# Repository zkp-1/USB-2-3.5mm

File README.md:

# USB-2-3.5mm
Personal Project to drive analog speakers from USB Type C.
##
I utilized a Cmedia CM108B audio IC and a MAX97720A Amplifier IC. The USB Type C connector is wired with resistors on CC1 and CC2 to allow power draw from the Host. The Cmedia IC then sends an identifier notifying the Host that the device is an audio device, making it load drivers and prepare for audio playthrough. A 90Ω impedance was aimed for in the design, to allow optimal operation on the differential USB data rails. At last, the IC sends the Audio data through its own DACs and internal amplifiers, converting it to analog and being able to be used at the intended 3.5mm output. 

The MAX97220A is set with a gain of 3.52dB and an input impedance of 10k. The output of the MAX IC is wired directly onto the 3.5mm and has an integrated anti-crackle and pop solution inside the IC, which was my main drive to using this IC for amplification.
# PCB 3D KiCAD Renders
1. 

2.

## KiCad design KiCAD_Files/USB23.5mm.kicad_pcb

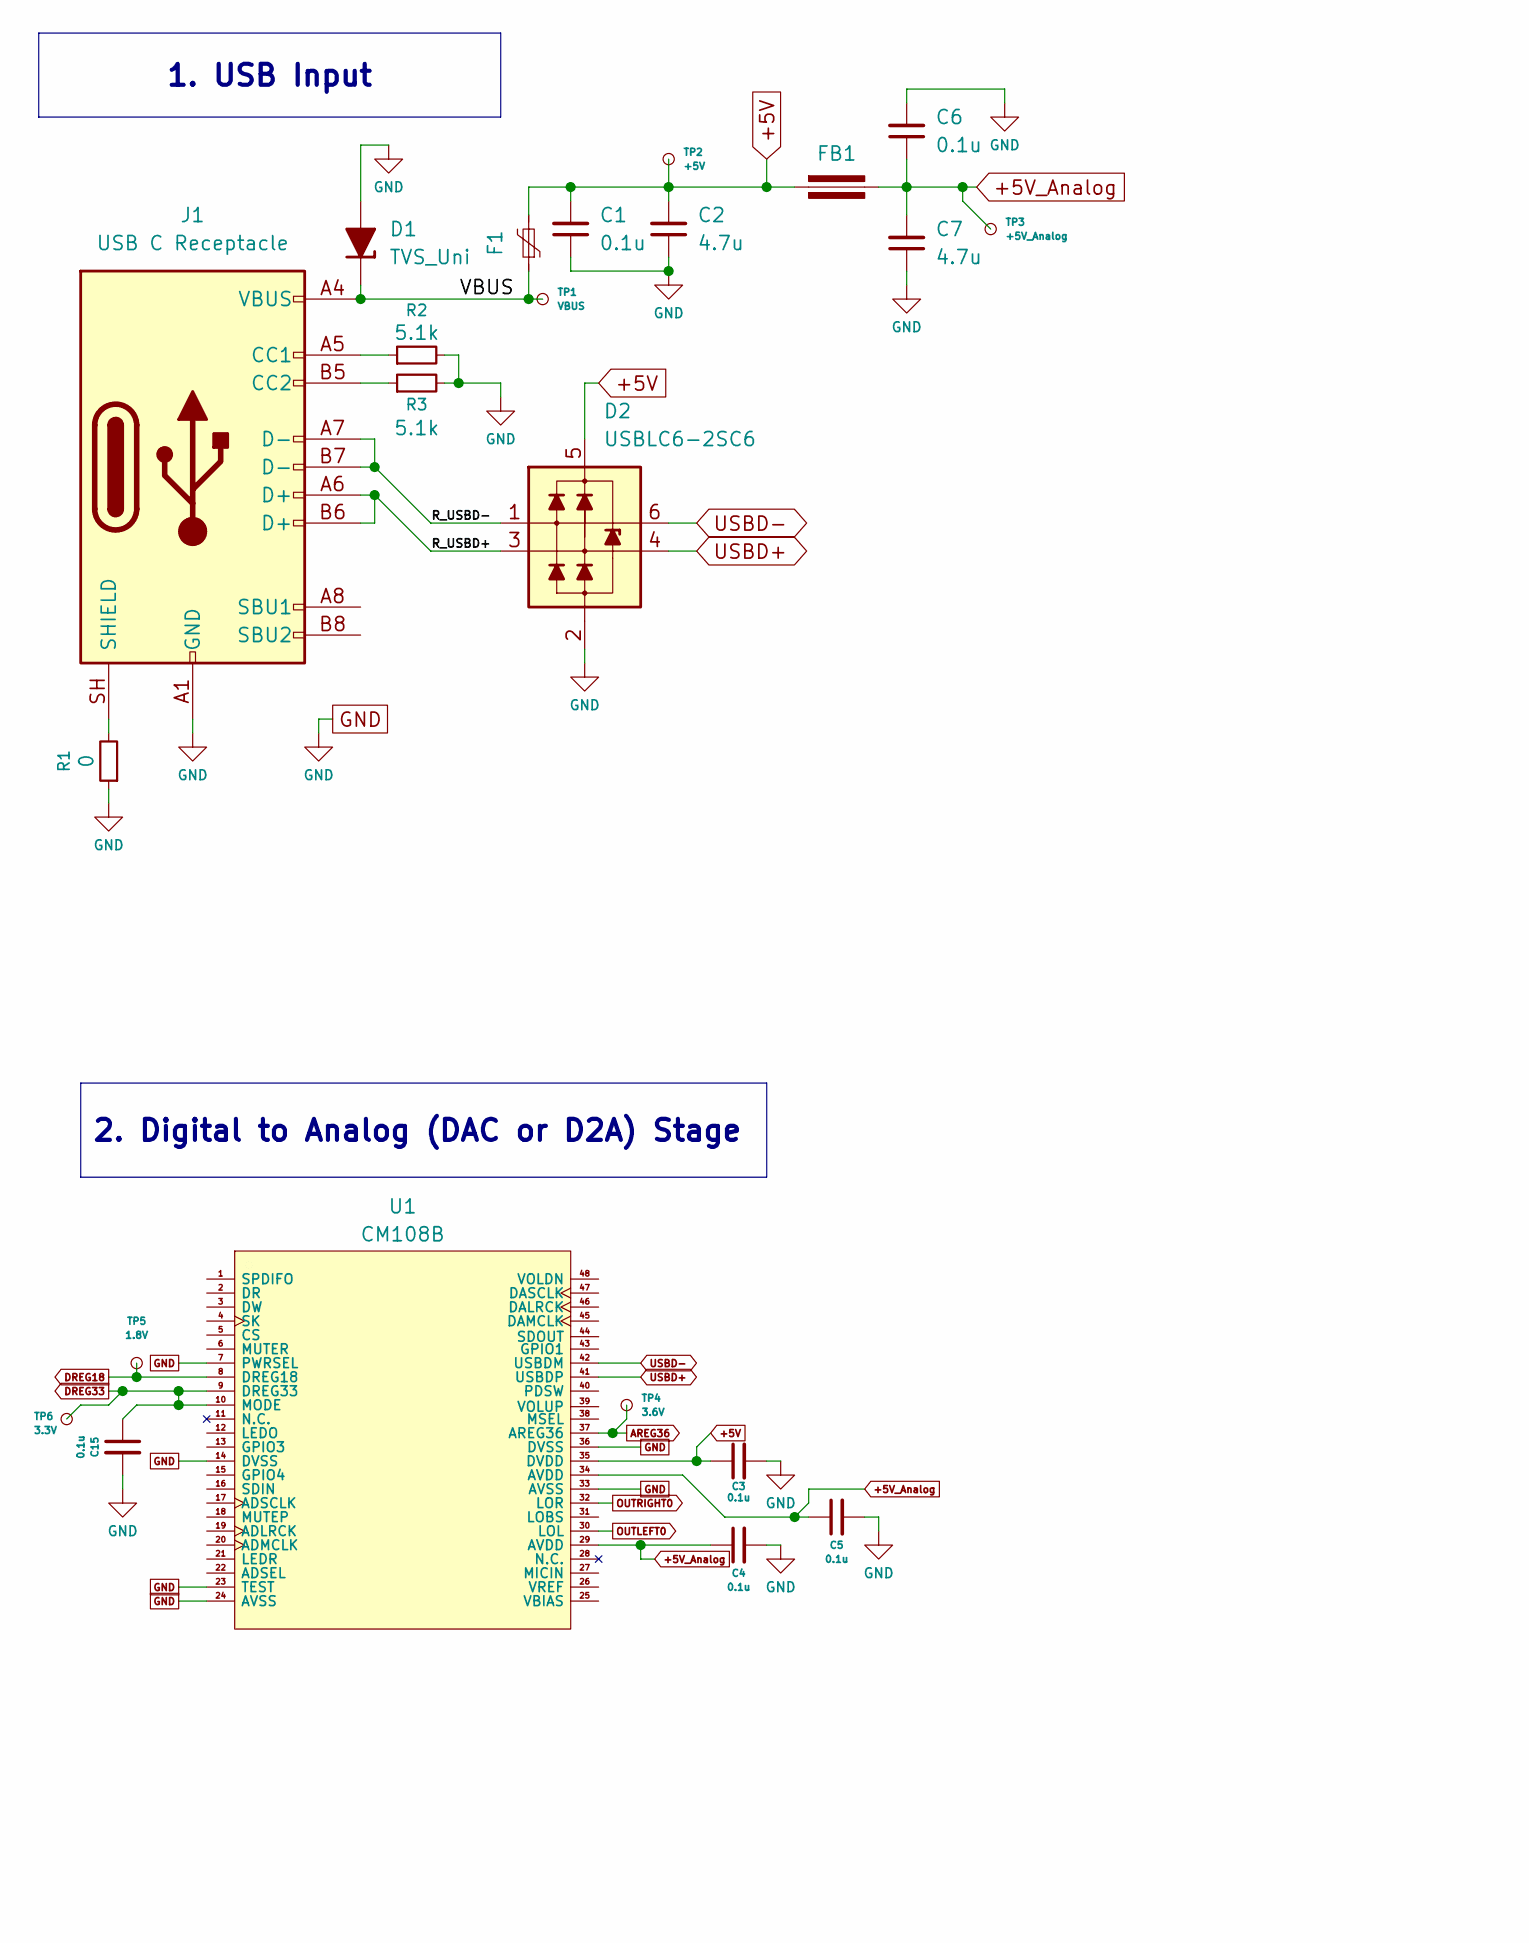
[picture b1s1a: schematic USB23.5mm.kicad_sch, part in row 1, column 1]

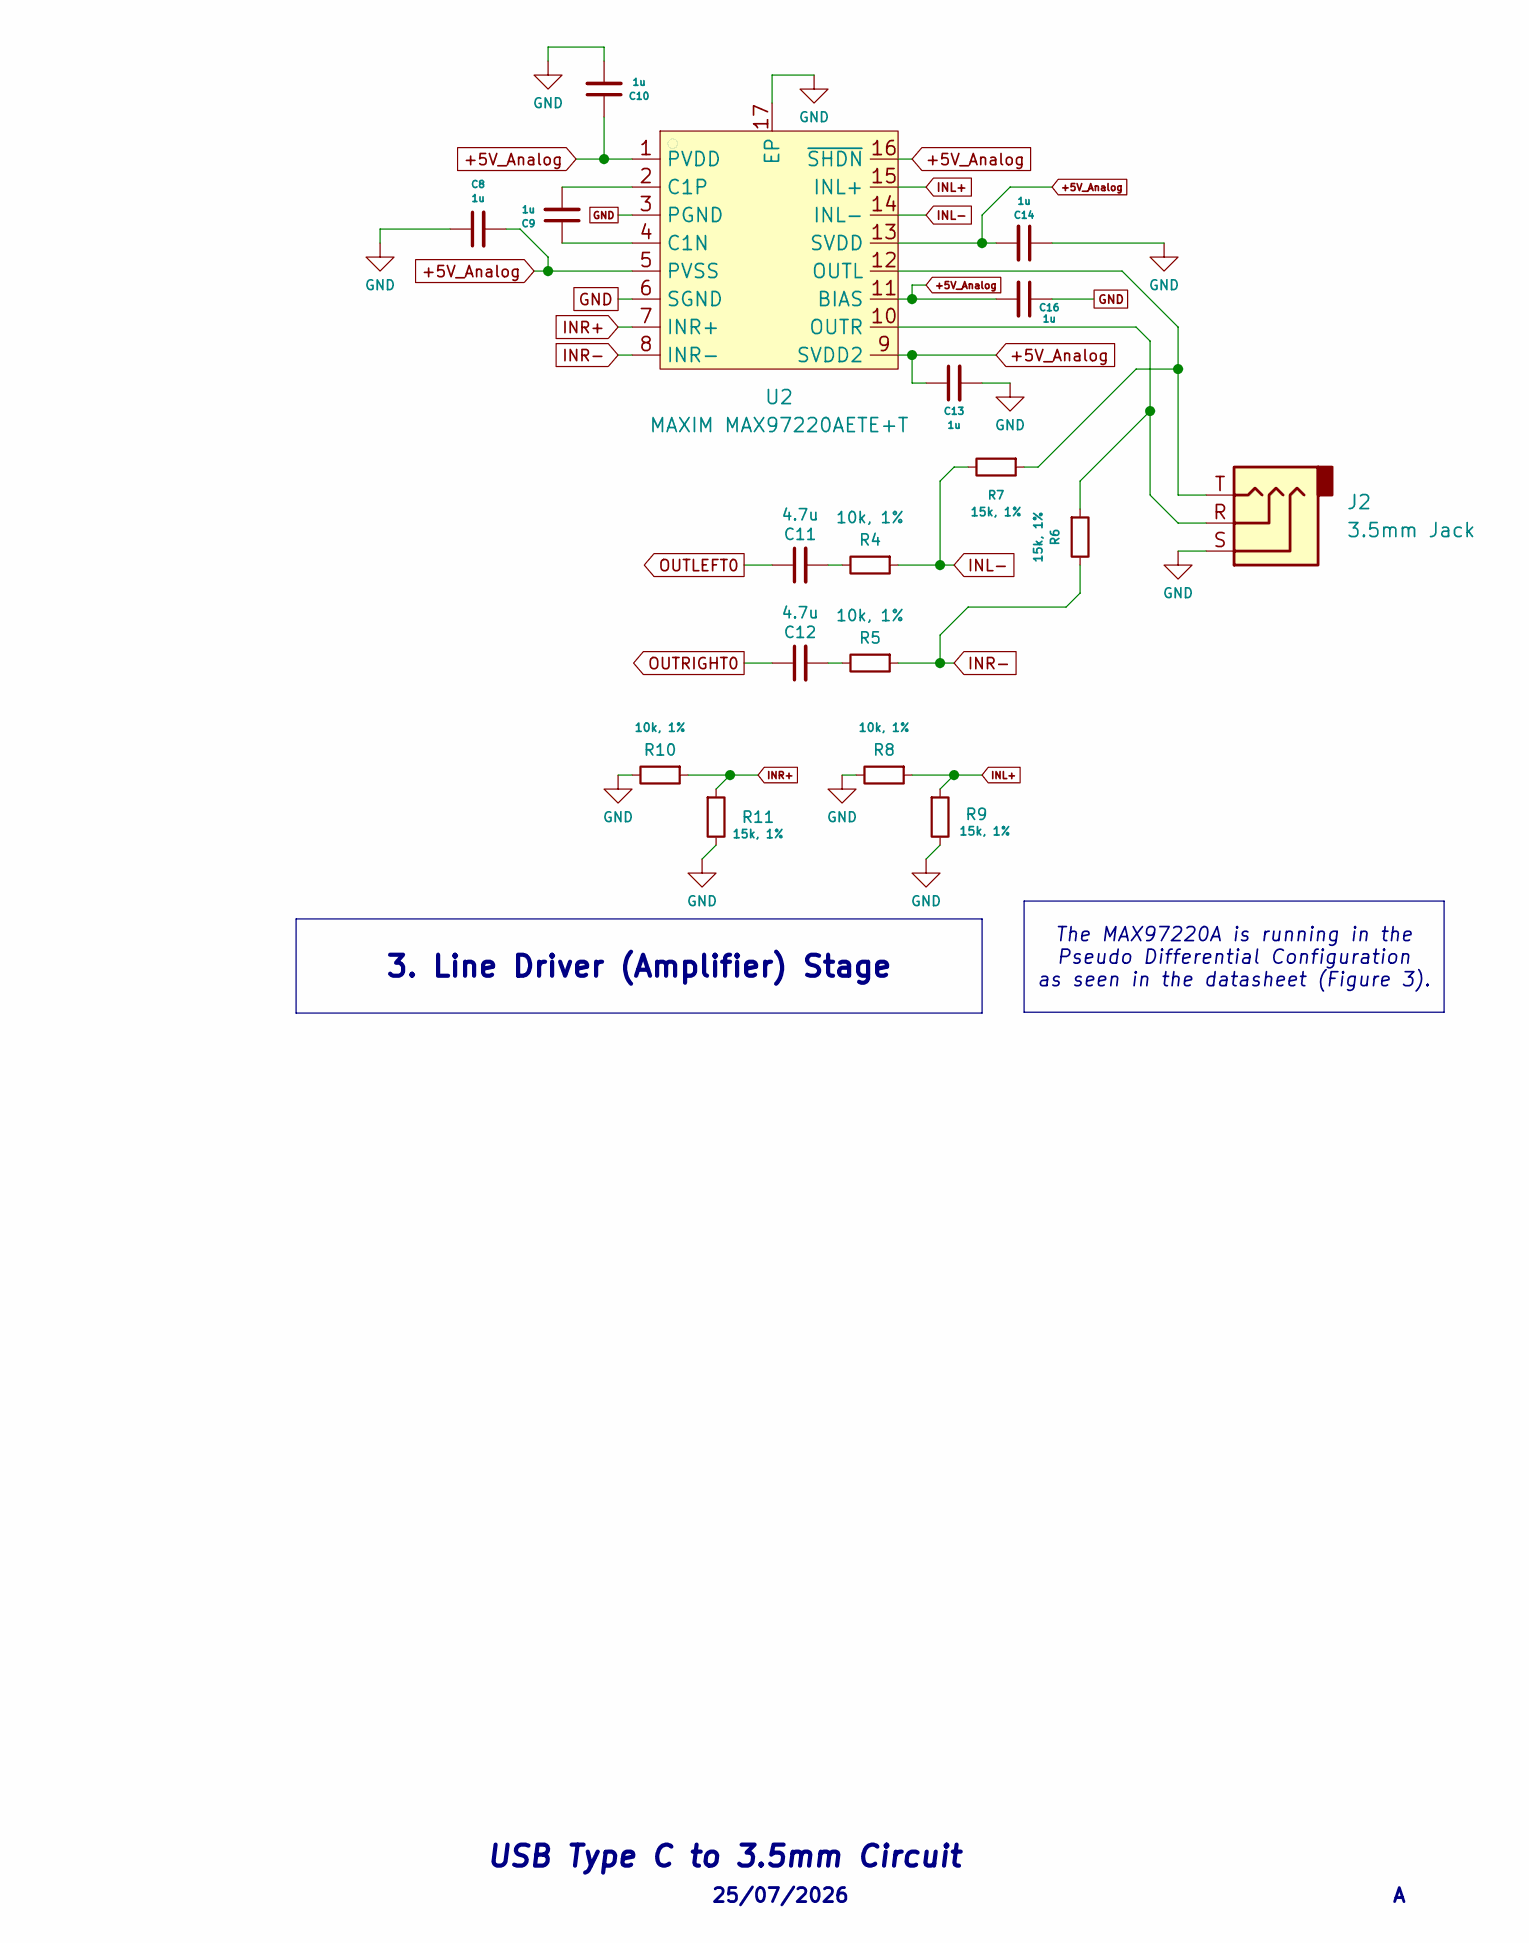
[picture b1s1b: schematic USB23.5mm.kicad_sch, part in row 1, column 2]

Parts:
C1, C3, C4, C5, C6, C15: 0.1u; C_0805_2012Metric_Pad1.18x1.45mm_HandSolder
C2, C7, C11, C12: 4.7u; C_0805_2012Metric_Pad1.18x1.45mm_HandSolder
C8, C9, C10, C13, C14, C16: 1u; C_0805_2012Metric_Pad1.18x1.45mm_HandSolder
D1: TVS_Uni; D_SOD-123F
D2: USBLC6-2SC6; SOT-23-6
F1: Polyfuse_S; Fuse_2920_7451Metric_Pad2.10x5.45mm_HandSolder
FB1: Ferrite_Bead; Ferrite_0805_2012Metric
J1: USB C Receptacle; USB_C_Receptacle_XKB_U262-16XN-4BVC11
J2: 3.5mm Jack; Jack_3.5mm_CUI_SJ-3523-SMT_Horizontal
R1: 0; R_0805_2012Metric
R2, R3: 5.1k; R_0805_2012Metric
R4, R5, R8, R10: 10k, 1%; R_0805_2012Metric
R6, R7, R9, R11: 15k, 1%; R_0805_2012Metric
TP1: VBUS; TestPoint_Pad_D1.5mm
TP2: +5V; TestPoint_Pad_D1.5mm
TP3: +5V_Analog; TestPoint_Pad_D1.5mm
TP4: 3.6V; TestPoint_Pad_D1.5mm
TP5: 1.8V; TestPoint_Pad_D1.5mm
TP6: 3.3V; TestPoint_Pad_D1.5mm
U1: CM108B; LQFP-48_7x7mm_P0.5mm
U2: MAXIM MAX97220AETE+T; QFN-16-1EP_3x3mm_P0.5mm_EP1.45x1.45mm

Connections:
+5V: C1.2, C2.2, C3.1, D2.5 (VP), F1.2, FB1.1, TP2.1 (1_1), U1.35 (DVDD)
+5V_Analog: C4.1, C5.1, C6.1, C7.2, C8.2, C10.1, C13.1, C14.2, C16.2, FB1.2, TP3.1 (1_1), U1.29 (AVDD), U1.34 (AVDD), U2.1 (PVDD), U2.5 (PVSS), U2.9 (SVDD2), U2.11 (BIAS), U2.13 (SVDD), U2.16 (~SHDN)
/R_USBD+: D2.3 (L2), J1.A6 (D+), J1.B6 (D+)
/R_USBD-: D2.1 (L1), J1.A7 (D-), J1.B7 (D-)
/VBUS: D1.1 (K), F1.1, J1.A4 (VBUS), J1.A9 (VBUS), J1.B4 (VBUS), J1.B9 (VBUS), TP1.1 (1_1)
AREG36: TP4.1 (1_1), U1.37 (AREG36)
DREG18: TP5.1 (1_1), U1.8 (DREG18)
DREG33: C15.1, TP6.1 (1_1), U1.9 (DREG33), U1.10 (MODE)
GND: C1.1, C2.1, C3.2, C4.2, C5.2, C6.2, C7.1, C8.1, C10.2, C13.2, C14.1, C15.2, C16.1, D1.2 (A), D2.2 (VN), J1.A1 (GND), J1.A12 (GND), J1.B1 (GND), J1.B12 (GND), J2.S, R1.1, R2.2, R3.2, R8.2, R9.2, R10.2, R11.2, U1.7 (PWRSEL), U1.14 (DVSS), U1.23 (TEST), U1.24 (AVSS), U1.33 (AVSS), U1.36 (DVSS), U2.3 (PGND), U2.6 (SGND), U2.17 (EP)
INL+: R8.1, R9.1, U2.15 (INL+)
INL-: R4.1, R7.2, U2.14 (INL-)
INR+: R10.1, R11.1, U2.7 (INR+)
INR-: R5.1, R6.2, U2.8 (INR-)
unnamed: C11.2, R4.2
unnamed: C12.2, R5.2
unnamed: J1.A5 (CC1), R2.1
unnamed: J1.B5 (CC2), R3.1
unnamed: J1.SH (SHIELD), R1.2
unnamed: C9.1, U2.4 (C1N)
unnamed: C9.2, U2.2 (C1P)
unnamed: J2.T, R7.1, U2.12 (OUTL)
unnamed: J2.R, R6.1, U2.10 (OUTR)
OUTLEFT0: C11.1, U1.30 (LOL)
OUTRIGHT0: C12.1, U1.32 (LOR)
USBD+: D2.4 (L2), U1.41 (USBDP)
USBD-: D2.6 (L1), U1.42 (USBDM)

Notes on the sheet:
25/07/2026
USB Type C to 3.5mm Circuit
1. USB Input
2. Digital to Analog (DAC or D2A) Stage
The MAX97220A is running in the Pseudo Differential Configuration as seen in the datasheet (Figure 3).
3. Line Driver (Amplifier) Stage

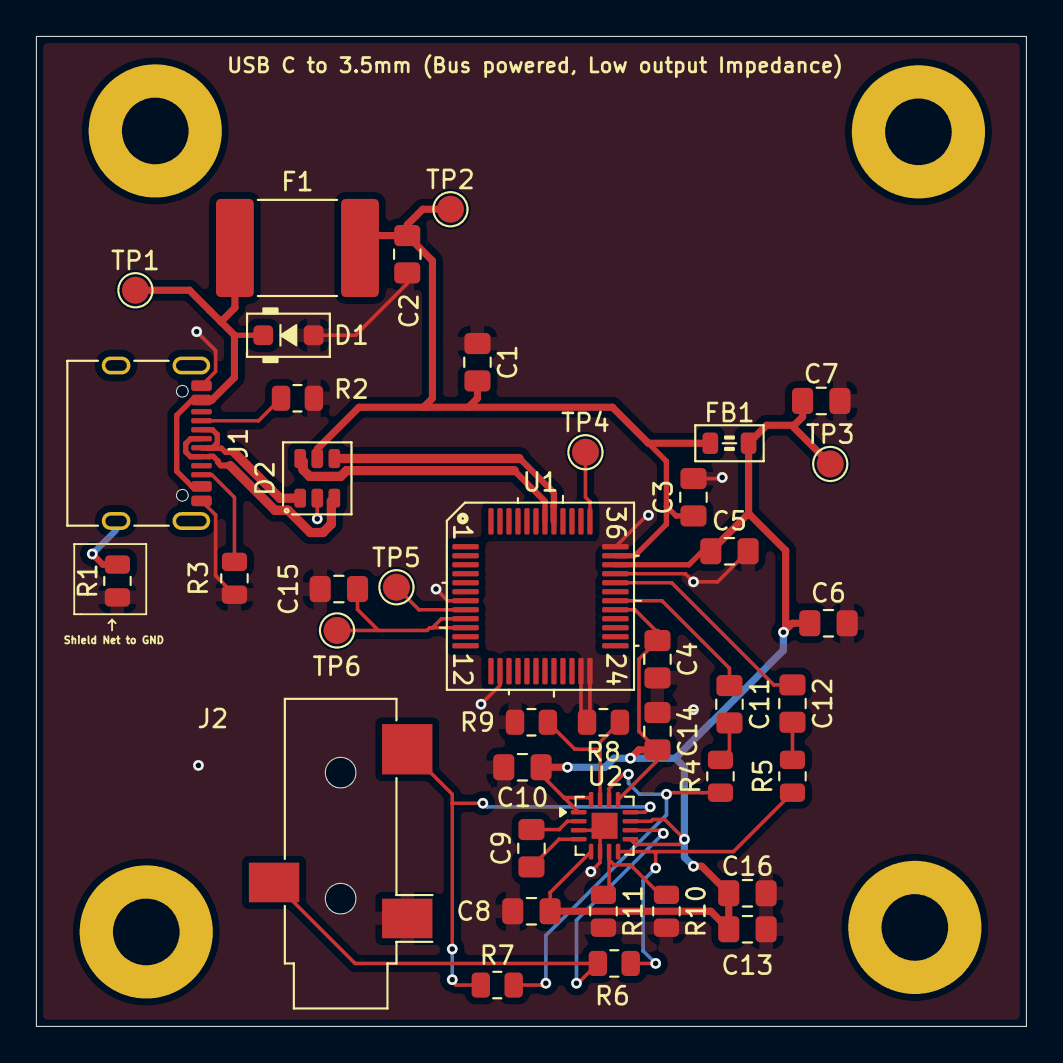
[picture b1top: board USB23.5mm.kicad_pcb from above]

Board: 2 copper layers, 55.0 x 55.0 mm, 41 parts (0 on the bottom side), 26 nets.

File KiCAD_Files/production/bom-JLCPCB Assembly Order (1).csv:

JLCPCB BOM Tool - BOM Matching,,,,,,,,,,,,,,,,,
BOM name：bom-JLCPCB Assembly Order.xlsx,,,Download Time：2026-07-26 06:23:22,,,,"* Our matching results are updated in real-time, but stock and prices may change. 
If it's been over 24 hours, please re-match before placing your order.",,,,,,,,,,
PCB Assembled Qty：5,,,Est. Total Price：30.8657,,,,,,,,,,,,,,
Your BOM,,,,,Matched Parts,,,,,,,Order Information,,,,,
Top Designator,Bottom Designator,Comment,Footprint,JLCPCB Part #,Matches,Part # ,Manufacturer,Footprint,Description,Category,Warning,JLCPCB Part #,Product link,Lib Type,Qty,Source,Total Price ($)
"C1,C15,C3,C4,C5,C6",,0.1u,0805,,Select by Customer,TCC0805X7R104K500DT,CCTC,0805,100nF 50V X7R ±10% 0805 Multilayer Ceramic Capacitors MLCC - SMD/SMT ROHS,Multilayer Ceramic Capacitors MLCC - SMD/SMT,1.The comment (TCC0805X7R104K500DT) of this part does not match the one (0.1u) provided in your BOM. Please confirm;,C282732,https://jlcpcb.com/partdetail/CCTC-TCC0805X7R104K500DT/C282732,Extended,40,40 JLCPCB,0.496
"C10,C13,C14,C16,C8,C9",,1u,0805,,Select by Customer,CGA0805X7R105K500KT,HRE,0805,1uF 50V X7R ±10% 0805 Multilayer Ceramic Capacitors MLCC - SMD/SMT ROHS,Multilayer Ceramic Capacitors MLCC - SMD/SMT,1.The comment (CGA0805X7R105K500KT) of this part does not match the one (1u) provided in your BOM. Please confirm;,C49056147,https://jlcpcb.com/partdetail/HRE-CGA0805X7R105K500KT/C49056147,Extended,36,36 JLCPCB,0.4284
"C11,C12,C2,C7",,4.7u,0805,,Select by Customer,TCC0805X7R475M500FT,CCTC,0805,4.7uF 50V X7R ±20% 0805 Multilayer Ceramic Capacitors MLCC - SMD/SMT ROHS,Multilayer Ceramic Capacitors MLCC - SMD/SMT,1.The comment (TCC0805X7R475M500FT) of this part does not match the one (4.7u) provided in your BOM. Please confirm;,C20416437,https://jlcpcb.com/partdetail/CCTC-TCC0805X7R475M500FT/C20416437,Extended,26,26 JLCPCB,3.484
D1,,TVS_Uni,D_SOD-123F,,Select by Customer,M4SMF15CA,Slkor(SLKORMICRO Elec.),SOD-123FL,15V 18.5V 180A@8/20us 1uA 26V 500pF Bidirectional TVS SOD-123FL ESD and Surge Protection (TVS/ESD) ROHS,,,C46061815,https://jlcpcb.com/partdetail/Slkor_SLKORMICRO_Elec-M4SMF15C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,Extended,15,15 JLCPCB,0.624
D2,,USBLC6-2SC6,SOT-23-6,,Select by System,USBLC6-2SC6,TECH PUBLIC,SOT-23-6,-55℃~+125℃ 0.35pF 12V 150W 2 5V 6A 6V 80nA ESD IEC 61000-4-2、IEC 61000-4-5、IEC 61000-4-4 Unidirectional SOT-23-6 ESD and Surge Protection (TVS/ESD) ROHS,ESD And Surge Protection (TVS/ESD),,C2827654,https://jlcpcb.com/partdetail/TECHPUBLIC-USBLC62SC6/C2827654,Extended,9,9 JLCPCB,0.3978
F1,,Polyfuse_S,2920,,Select by Customer,2920L500/6GR,LUTE,2920,-40℃~+85℃ 1.6mm 10A 2.5W 31mΩ 40A 5.44mm 5A 5mΩ 5s 6V 7.98mm 2920 Resettable Fuses ROHS,Resettable Fuses,,C19193059,https://jlcpcb.com/partdetail/LUTE-2920L5006GR/C19193059,Extended,5,5 JLCPCB,0.744
FB1,,Ferrite_Bead,Ferrite_0805_2012Metric,,Select by Customer,ZECB201209A121-4A000,ZE,0805,1 120Ω@100MHz 4A 50mΩ ±25% 0805 Ferrite Beads ROHS,Inductors (SMD),,C2943443,https://jlcpcb.com/partdetail/ZE-ZECB201209A1214A000/C2943443,Extended,20,20 JLCPCB,0.89
J1,,USBCReceptacle,USB_C_Receptacle_XKB_U262-16XN-4BVC11,,Select by Customer,HX TYPE-C 16PIN,hanxia,SMD,"-30℃~+80℃ 1 1.68mm 16P 20V 3A 5,000 times 7.35mm Black Female Surface Mount, Right Angle Type-C USB 3.1 SMD USB Connectors ROHS",USB Connectors,,C5178539,https://jlcpcb.com/partdetail/hanxia-HX_TYPE_C16PIN/C5178539,Extended,5,5 JLCPCB,0.375
J2,,3.5mmJack,Jack_3.5mm_CUI_SJ-3523-SMT_Horizontal,,Select by Customer,PJ-320B,SOFNG,SMD,-25℃~+75℃ 24V 25mA 3.5mm Headphone Jack Phosphor Bronze SMD Audio Connectors ROHS,Audio Connectors (Headphones),,C22355831,https://jlcpcb.com/partdetail/SOFNG-PJ320B/C22355831,Extended,5,5 JLCPCB,0.2455
R1,,0,0805,,Select by Customer,0805W8F0000T5E,UNI-ROYAL(Uniroyal Elec),0805,-55℃~+155℃ 0Ω 125mW 150V Thick Film Resistor ±1% ±800ppm/℃ 0805 Chip Resistor - Surface Mount ROHS,Chip Resistor - Surface Mount,1.The comment (0805W8F0000T5E) of this part does not match the one (0) provided in your BOM. Please confirm;,C17477,https://jlcpcb.com/partdetail/18165-0805W8F0000T5E/C17477,Basic,20,20 JLCPCB,0.2
"R2,R3",,5.1k,0805,,Select by Customer,GR0805F5K1T5G00,GiantOhm,0805,-55℃~+155℃ 125mW 150V 5.1kΩ Thick Film Resistor ±1% 0805 Chip Resistor - Surface Mount ROHS,,1.The comment (GR0805F5K1T5G00) of this part does not match the one (5.1k) provided in your BOM. Please confirm;,C49653299,https://jlcpcb.com/partdetail/GiantOhm-GR0805F5K1T5G00/C49653299,Extended,20,20 JLCPCB,0.034
"R10,R4,R5,R8",,"10k,1%",0805,,Select by Customer,HRC0805F1002FNTN,HWA CHN,0805,-55℃~+155℃ 10kΩ 125mW 150V Thick Film Resistor ±1% ±100ppm/℃ 0805 Chip Resistor - Surface Mount ROHS,,"1.The comment (HRC0805F1002FNTN) of this part does not match the one (10k,1%) provided in your BOM. Please confirm;",C54921094,https://jlcpcb.com/partdetail/HWACHN-HRC0805F1002FNTN/C54921094,Extended,26,26 JLCPCB,0.052
"R11,R6,R7,R9",,"15k,1%",0805,,Select by Customer,SC0805F1502F4ANRH,Sunway,0805,-55℃~+155℃ 125mW 150V 15kΩ Thick Film Resistor ±1% ±100ppm/℃ 0805 Chip Resistor - Surface Mount ROHS,Chip Resistor - Surface Mount,"1.The comment (SC0805F1502F4ANRH) of this part does not match the one (15k,1%) provided in your BOM. Please confirm;",C5140930,https://jlcpcb.com/partdetail/Sunway-SC0805F1502F4ANRH/C5140930,Extended,30,30 JLCPCB,0.036
U1,,CM108B,LQFP-48_7x7mm_P0.5mm,,Select by System,CM108B,Cmedia,LQFP-48(7x7),-20℃~+70℃ 4.5V~5.5V 44.1kHz~48kHz Encoder/decoder I2S、USB LQFP-48(7x7) Audio Interface ICs ROHS,Audio Interface ICs,,C371347,https://jlcpcb.com/partdetail/Cmedia-CM108B/C371347,Extended,5,5 JLCPCB,16.2815
U2,,MAXIMMAX97220AETE+T,QFN-16-1EP_3x3mm_P0.5mm_EP1.45x1.45mm,,Select by Customer,MAX97220AETE+T,Analog Devices Inc./Maxim Integrated,QFN-16-EP(3x3),-40℃~+85℃ 0.0035% 112.5dB 125mWx2@32Ω 2-Channel 2.5V~5.5V 7mA 90dB Automatic mute/no-noise switch、Enable/disable function QFN-16-EP(3x3) Audio Amplifiers ROHS,Audio Amplifiers,,C2682711,https://jlcpcb.com/partdetail/2777742-MAX97220AETET/C2682711,Extended,5,5 JLCPCB,6.5775
TP1,,VBUS,TestPoint_Pad_D1.5mm,,No matches,No Part Selected,,,,,,,,,,,
TP2,,+5V,TestPoint_Pad_D1.5mm,,No matches,No Part Selected,,,,,,,,,,,
TP3,,+5V_Analog,TestPoint_Pad_D1.5mm,,No matches,No Part Selected,,,,,,,,,,,
TP4,,3.6V,TestPoint_Pad_D1.5mm,,No matches,No Part Selected,,,,,,,,,,,
TP5,,1.8V,TestPoint_Pad_D1.5mm,,No matches,No Part Selected,,,,,,,,,,,
TP6,,3.3V,TestPoint_Pad_D1.5mm,,No matches,No Part Selected,,,,,,,,,,,
"_3,_2",,,,,No matches,No Part Selected,,,,,,,,,,,
